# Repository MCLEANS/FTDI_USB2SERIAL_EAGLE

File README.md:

# FTDI_USB2SERIAL_EAGLE

An Implementation of USB to SERIAL converter using AutoDesk Eagle

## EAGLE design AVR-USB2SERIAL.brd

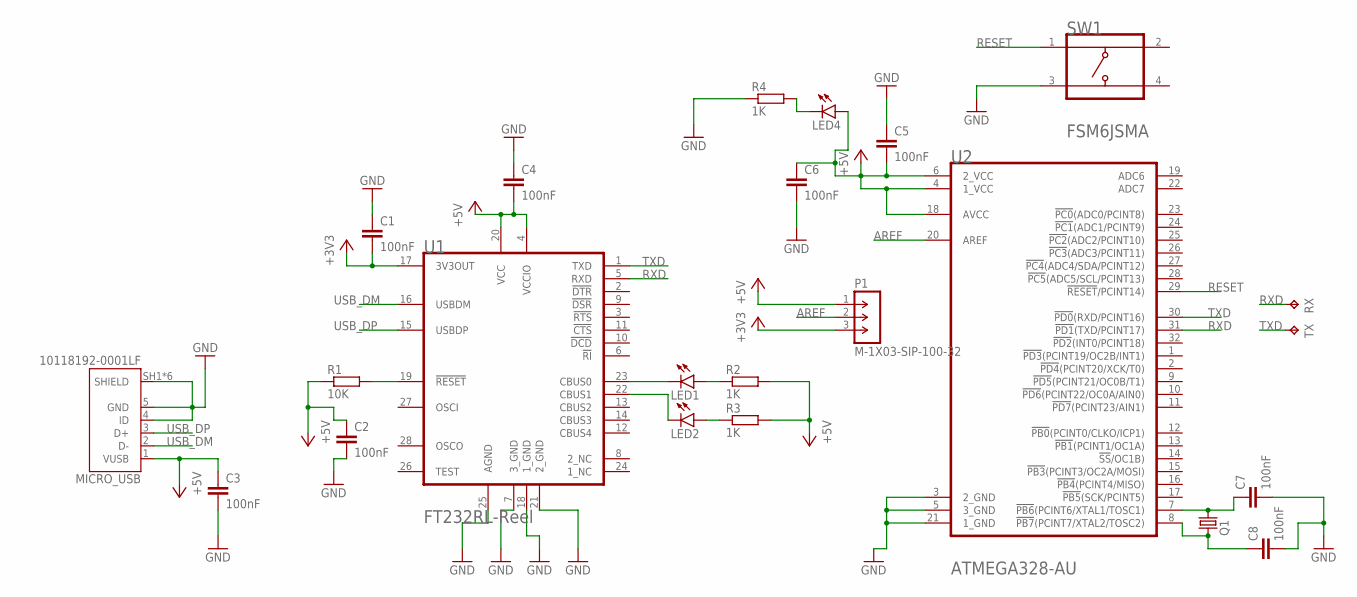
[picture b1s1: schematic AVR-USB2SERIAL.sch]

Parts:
C1, C2, C3, C4, C5, C6, C7, C8: 100nF; C0805
LED1, LED2, LED4: LEDCHIPLED_0805; CHIPLED_0805
MICRO_USB: 10118192-0001LF; AMPHENOL_10118192-0001LF
P1: M-1X03-SIP-100-32; SIP-100-03-32
Q1: CRYSTALHC49UP; HC49UP
R1: 10K; R0805
R2, R3, R4: 1K; R0805
RX: TPB1,27; B1,27
SW1: TE_CONNECTIVITY_ALCOSWITCH_FSM6JSMATE_CONNECTIVIT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; TE_CONNECTIVITY_ALCOSWITCH_FSM6JSMA_0
TX: TPB1,27; B1,27
U1: FTDI_FT232RL-REELFTDI_FT232RL-REEL_0_0; FTDI_FT232RL-REEL_0
U2: MICROCHIP_-_ATMEL_ATMEGA328-AUMICROCHIP_-_ATMEL_A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; MICROCHIP_-_ATMEL_ATMEGA328-AU_0

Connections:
+3V3: C1.2, P1.3, U1.17 (3V3OUT)
+5V: C2.1, C3.1, C4.2, C5.2, C6.1, LED4.A, MICRO_USB.1 (VUSB), P1.1, R1.1, R2.2, R3.2, U1.4 (VCCIO), U1.20 (VCC), U2.4 (1_VCC), U2.6 (2_VCC), U2.18 (AVCC)
AREF: P1.2, U2.20 (AREF)
GND: C1.1, C2.2, C3.2, C4.1, C5.1, C6.2, C7.2, C8.2, MICRO_USB.4 (ID), MICRO_USB.5 (GND), MICRO_USB.SH1 (SHIELD), MICRO_USB.SH2 (SHIELD), MICRO_USB.SH3 (SHIELD), MICRO_USB.SH4 (SHIELD), MICRO_USB.SH5 (SHIELD), MICRO_USB.SH6 (SHIELD), R4.1, SW1.3, U1.7 (3_GND), U1.18 (1_GND), U1.21 (2_GND), U1.25 (AGND), U2.3 (2_GND), U2.5 (3_GND), U2.21 (1_GND)
unnamed: LED1.A, R2.1
unnamed: R1.2, U1.19 (!RESET!)
unnamed: LED1.C, U1.23 (CBUS0)
unnamed: LED2.A, R3.1
unnamed: LED2.C, U1.22 (CBUS1)
unnamed: C7.1, Q1.2, U2.7 (!PB6!(PCINT6/XTAL1/TOSC1))
unnamed: C8.1, Q1.1, U2.8 (!PB7!(PCINT7/XTAL2/TOSC2))
unnamed: LED4.C, R4.2
RESET: SW1.1, U2.29 (!RESET!/PCINT14))
RXD: RX.TP, U1.5 (RXD), U2.31 (!PD1!(TXD/PCINT17))
TXD: TX.TP, U1.1 (TXD), U2.30 (!PD0!(RXD/PCINT16))
USB_DM: MICRO_USB.2 (D-), U1.16 (USBDM)
USB_DP: MICRO_USB.3 (D+), U1.15 (USBDP)

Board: 2 copper layers, 23 parts (0 on the bottom side), 17 nets, no tracks yet.

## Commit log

2020-05-03 Added MicroUSB and FTDI chip
2020-05-03 eagle project file
2020-05-03 Micro-controller connections
2020-05-03 completed common connections
2020-05-03 unrouted board
2020-05-18 project description
2020-05-18 Added description

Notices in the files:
parts and their libraries:
con-headers-jp: Copyright (C) 2008, Bob Starr
